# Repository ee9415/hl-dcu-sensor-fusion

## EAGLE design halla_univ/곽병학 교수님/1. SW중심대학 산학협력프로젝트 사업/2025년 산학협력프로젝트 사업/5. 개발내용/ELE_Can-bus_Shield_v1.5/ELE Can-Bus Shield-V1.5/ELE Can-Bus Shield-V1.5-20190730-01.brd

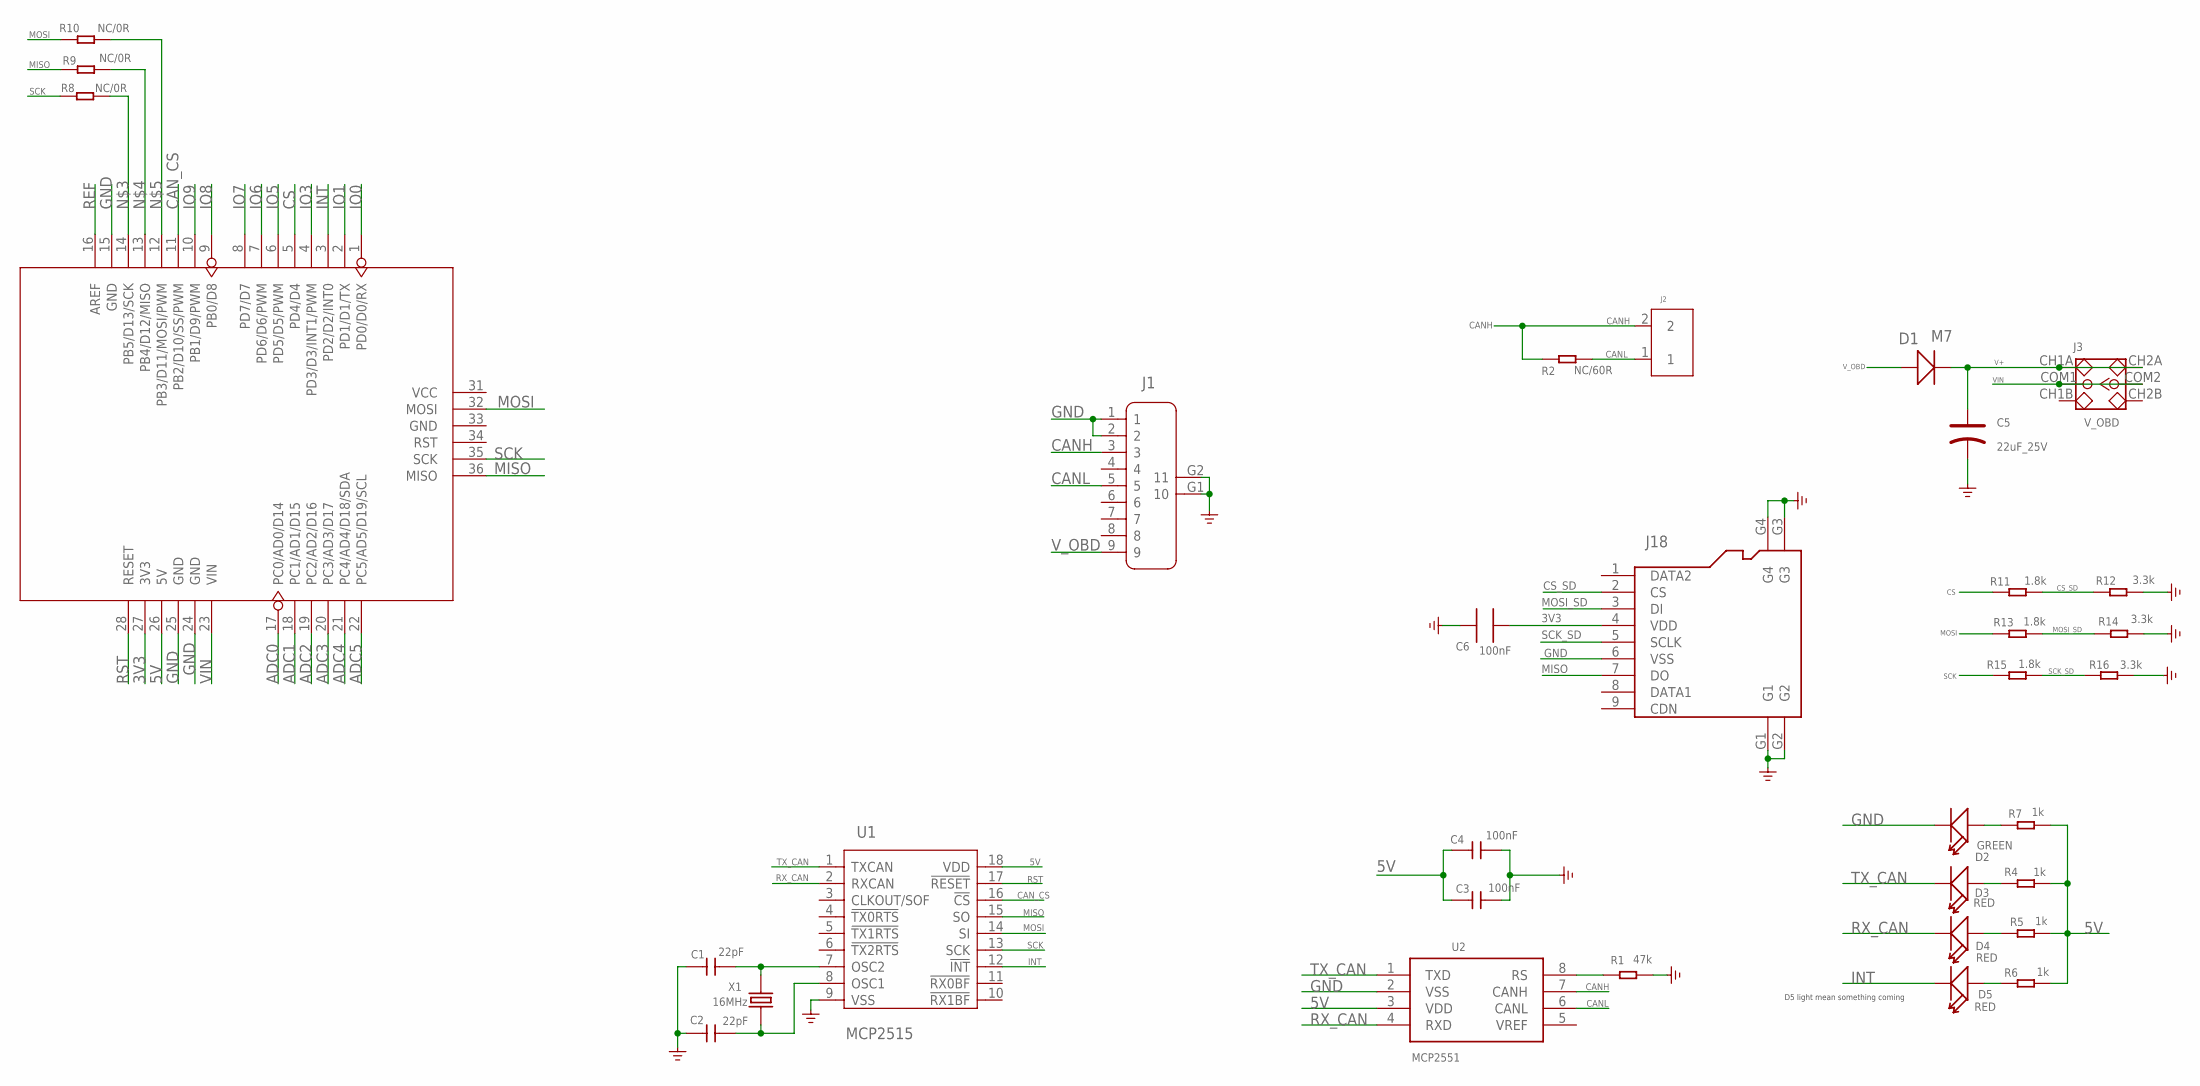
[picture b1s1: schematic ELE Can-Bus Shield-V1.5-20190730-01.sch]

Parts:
C1, C2: 22pF; 0603
C3, C4, C6: 100nF; 0603
C5: 22uF_25V; AVX-C
D1: M7; D2010
D2: GREEN; LED-0603
D3, D4, D5: RED; LED-0603
J1: DB9'MEAL'; DB9-MEAL
J2: SCREW-TERMINAL-2P5.0; 2P-5.0
J3: V_OBD; 6P-2CH-2.54-7.6X3.0
J18: HOLDER-MICROSD-9P; 9P-SMD-W/-RING
R1: 47k; R0603
R2: NC/60R; 0603
R4, R5, R6, R7: 1k; R0603
R8, R9, R10: NC/0R; DISCRETE_R0603
R11, R13, R15: 1.8k; 0603
R12, R14, R16: 3.3k; 0603
U1: MCP2515; SOIC18
U2: MCP2551; SO08
U4: ARDUINO
X1: 16MHz; HC49/S

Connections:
3V3: C6.2, J18.4 (VDD), U4.27 (3V3)
5V: C3.1, C4.1, R4.2, R5.2, R6.2, R7.2, U1.18 (VDD), U2.3 (VDD), U4.26 (5V)
ADC0: U4.17 (PC0/AD0/D14)
ADC1: U4.18 (PC1/AD1/D15)
ADC2: U4.19 (PC2/AD2/D16)
ADC3: U4.20 (PC3/AD3/D17)
ADC4: U4.21 (PC4/AD4/D18/SDA)
ADC5: U4.22 (PC5/AD5/D19/SCL)
CANH: J1.3, J2.2, R2.1, U2.7 (CANH)
CANL: J1.5, J2.1, R2.2, U2.6 (CANL)
CAN_CS: U1.16 (!CS), U4.11 (PB2/D10/SS/PWM)
CS: R11.1, U4.5 (PD4/D4)
CS_SD: J18.2 (CS), R11.2, R12.1
GND: C1.1, C2.1, C3.2, C4.2, C5.-, C6.1, D2.-, J1.1, J1.2, J1.G1 (10), J1.G2 (11), J18.6 (VSS), J18.G1, J18.G2, J18.G3, J18.G4, R1.2, R12.2, R14.2, R16.2, U1.9 (VSS), U2.2 (VSS), U4.15 (GND), U4.24 (GND), U4.25 (GND)
INT: D5.-, U1.12 (!INT), U4.3 (PD2/D2/INT0)
IO0: U4.1 (PD0/D0/RX)
IO1: U4.2 (PD1/D1/TX)
IO3: U4.4 (PD3/D3/INT1/PWM)
IO5: U4.6 (PD5/D5/PWM)
IO6: U4.7 (PD6/D6/PWM)
IO7: U4.8 (PD7/D7)
IO8: U4.9 (PB0/D8)
IO9: U4.10 (PB1/D9/PWM)
MISO: J18.7 (DO), R9.2, U1.15 (SO), U4.36 (MISO)
MOSI: R10.2, R13.1, U1.14 (SI), U4.32 (MOSI)
MOSI_SD: J18.3 (DI), R13.2, R14.1
unnamed: D2.+, R7.1
unnamed: D3.+, R4.1
unnamed: R8.1, U4.14 (PB5/D13/SCK)
unnamed: R9.1, U4.13 (PB4/D12/MISO)
unnamed: R10.1, U4.12 (PB3/D11/MOSI/PWM)
unnamed: D4.+, R5.1
unnamed: C1.2, U1.7 (OSC2), X1.2
unnamed: C2.2, U1.8 (OSC1), X1.1
unnamed: D5.+, R6.1
unnamed: R1.1, U2.8 (RS)
REF: U4.16 (AREF)
RST: U1.17 (!RESET), U4.28 (RESET)
RX_CAN: D4.-, U1.2 (RXCAN), U2.4 (RXD)
SCK: R8.2, R15.1, U1.13 (SCK), U4.35 (SCK)
SCK_SD: J18.5 (SCLK), R15.2, R16.1
TX_CAN: D3.-, U1.1 (TXCAN), U2.1 (TXD)
V+: C5.+, D1.-, J3.CH1A, J3.CH2A
VIN: J3.COM1, J3.COM2, U4.23 (VIN)
V_OBD: D1.+, J1.9

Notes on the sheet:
D5 light mean something coming

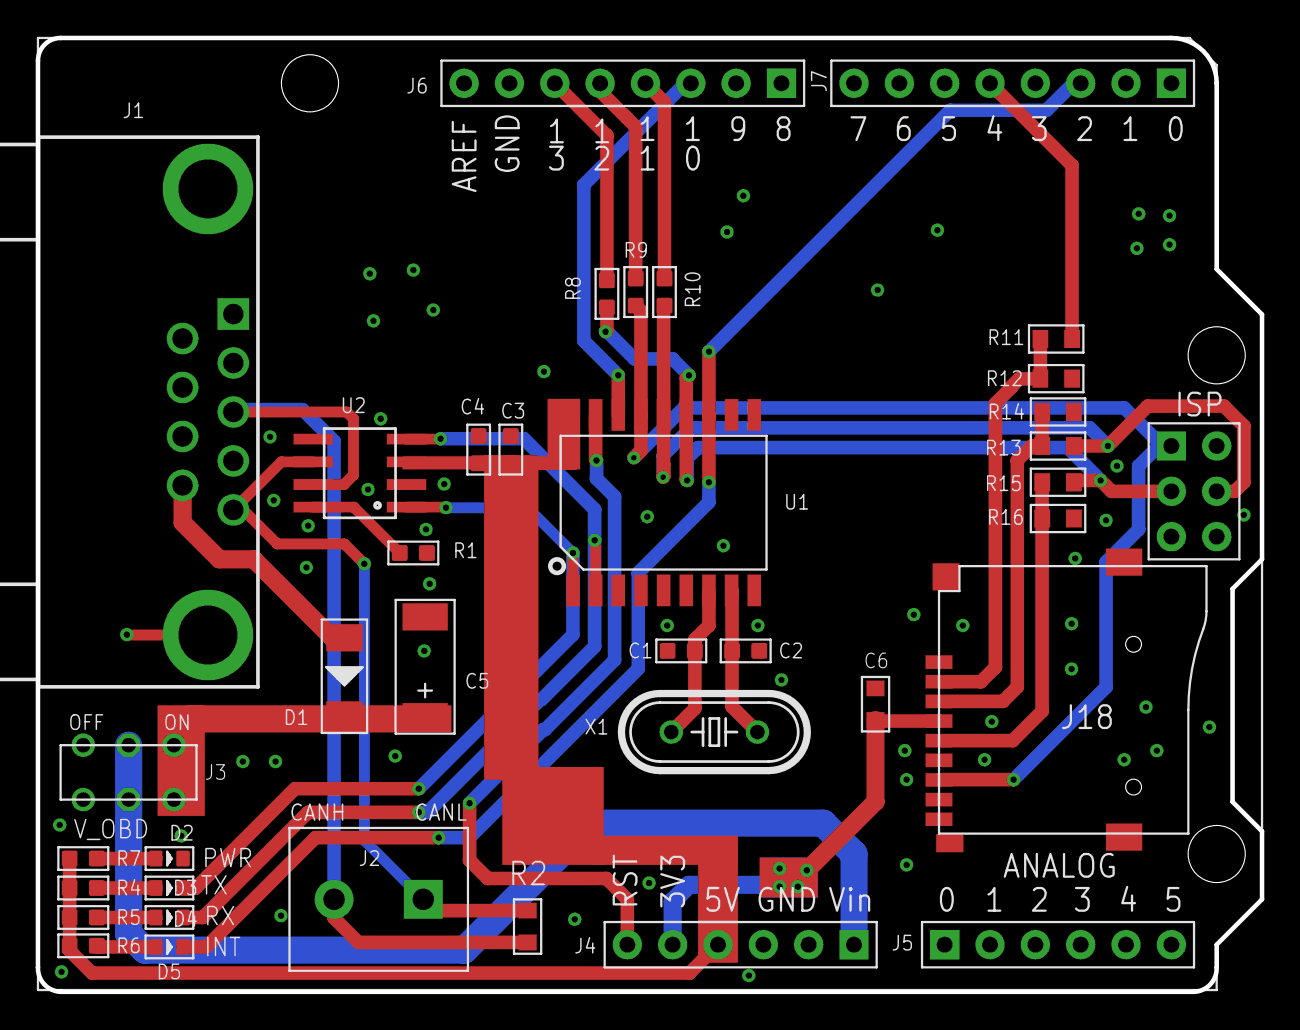
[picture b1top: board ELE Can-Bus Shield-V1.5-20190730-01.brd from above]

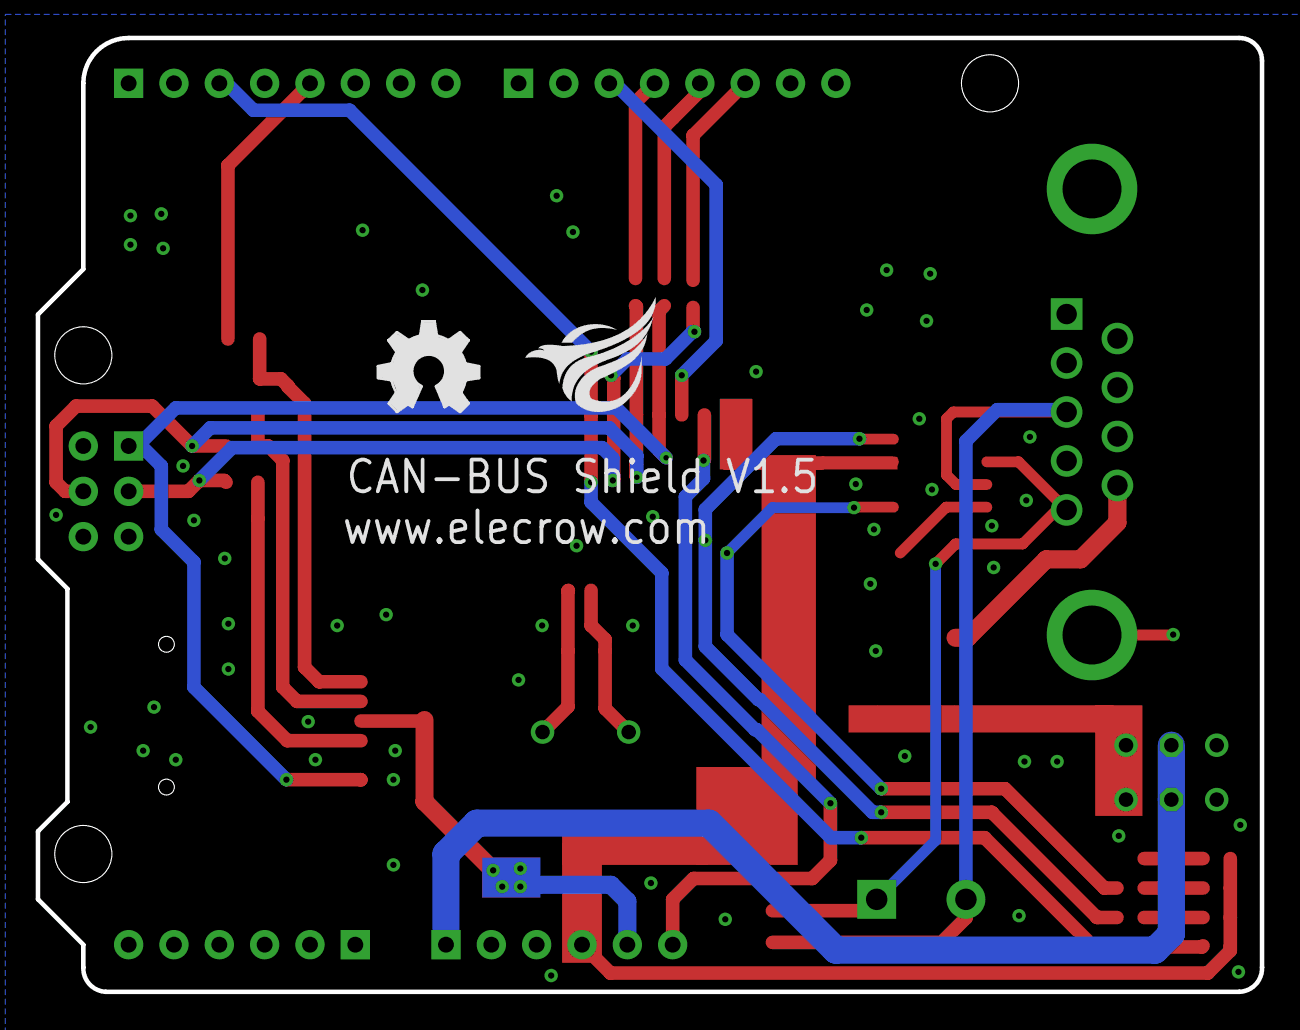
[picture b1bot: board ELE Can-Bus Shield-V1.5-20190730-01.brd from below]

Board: 2 copper layers, 68.6 x 53.4 mm, 36 parts (2 on the bottom side), 30 nets.

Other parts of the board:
U$1: ELECROW_NRW_6
U$2: OSHW_FILLX200_NOTEXT
